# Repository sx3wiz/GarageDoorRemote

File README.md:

# GarageDoorRemote

This project is an OSHW garage door keychain remote and receiver. This project is not garage door opener brand specific. It takes advantage of the fact that almost all garage dooor openers have a NO contact input to trigger a opening/closing cycle.

## Project Goals

1. Small remote form factor
 * Keychain sized
2. Long battery life on remote
3. High security
 * No replay attacks
 * Secure encryption during pairing
3. Decent range
 * About 25 meters

## Directory Structure
* hardware/
 * Contains all OSHW designs for the remote and receiver
* software/
 * Contains all software for remote and receiver

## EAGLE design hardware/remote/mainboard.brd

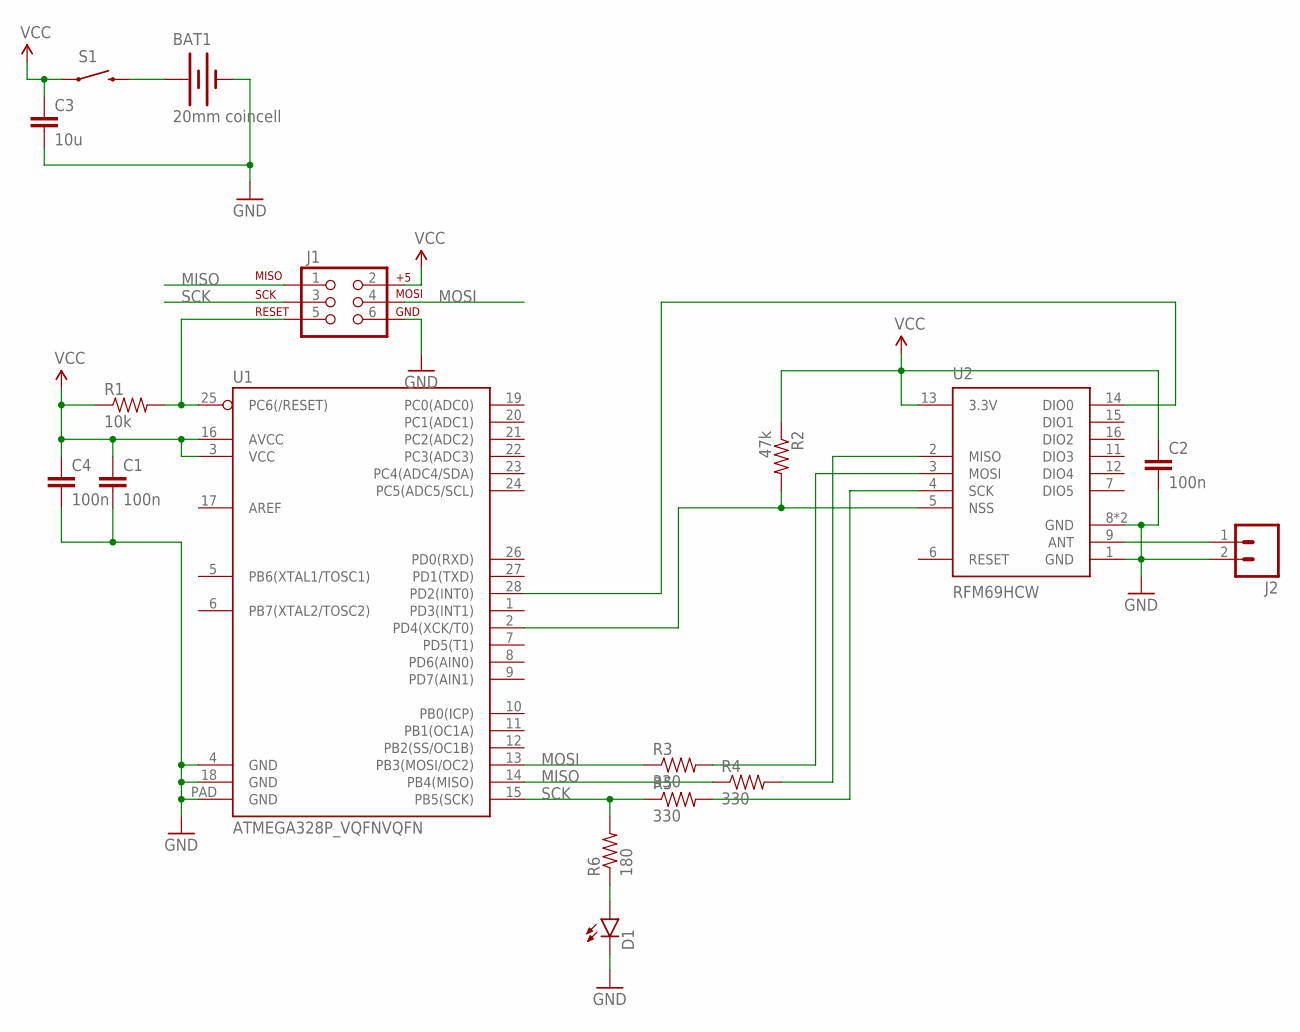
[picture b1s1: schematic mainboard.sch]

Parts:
BAT1: 20mm coincell; BATTCON_20MM_4LEGS
C1, C2, C4: 100n; 0603-CAP
C3: 10u; 1206
D1: LED0603; LED-0603
J1: AVR_SPI_PRG_6PTH; 2X3
J2: M02PTH; 1X02
R1: 10k; 0603-RES
R2: 47k; 0603-RES
R3, R4, R5: 330; 0603-RES
R6: 180; 0603-RES
S1: SWITCH-MOMENTARY-2PTH; TACTILE-PTH
U1: ATMEGA328P_VQFNVQFN; VQFN-28
U2: RFM69HCW; RFM69HCW-XXXS2

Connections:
GND: BAT1.NEGATIVE (-), C1.2, C2.2, C3.2, C4.2, D1.C, J1.6, J2.2, U1.4 (GND), U1.18 (GND), U1.PAD (GND), U2.1 (GND), U2.8 (GND), U2.10 (GND)
MISO: J1.1, R4.1, U1.14 (PB4(MISO))
MOSI: J1.4, R3.1, U1.13 (PB3(MOSI/OC2))
unnamed: BAT1.POSITIVE@1 (+), BAT1.POSITIVE@2 (+), BAT1.POSITIVE@3 (+), BAT1.POSITIVE@4 (+), S1.3 (2)
unnamed: J1.5, R1.2, U1.25 (PC6(/RESET))
unnamed: R3.2, U2.3 (MOSI)
unnamed: J2.1, U2.9 (ANT)
unnamed: R4.2, U2.2 (MISO)
unnamed: R2.2, U1.2 (PD4(XCK/T0)), U2.5 (NSS)
unnamed: R5.2, U2.4 (SCK)
unnamed: U1.28 (PD2(INT0)), U2.14 (DIO0)
unnamed: D1.A, R6.1
SCK: J1.3, R5.1, R6.2, U1.15 (PB5(SCK))
VCC: C1.1, C2.1, C3.1, C4.1, J1.2, R1.1, R2.1, S1.1, U1.3 (VCC), U1.16 (AVCC), U2.13 (3.3V)

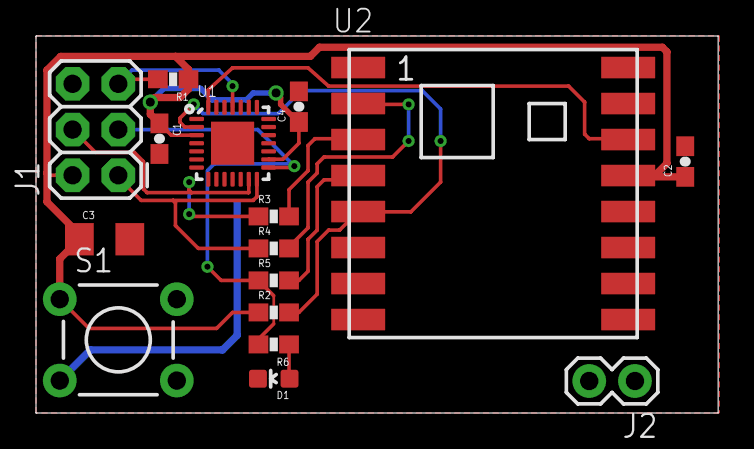
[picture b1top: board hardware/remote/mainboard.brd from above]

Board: 2 copper layers, 37.9 x 20.9 mm, 17 parts (1 on the bottom side), 14 nets.

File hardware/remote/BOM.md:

# Bill of materials

### Version vX.X

Componet Refs  | Type            | Value       | Package  | Qty | Digikey Part #
---------------|-----------------|-------------|----------|-----|---------------
U1             | microcontroller | n/a         | 28-VQFN  | 1   | ATMEGA328P-MMH-ND
U2             | transceiver     | 433mhz      | 16-smd   | 1   | 1568-1391-ND
R1             | resistor        | 10k         | 0603     | 1   | 311-10.0KLRCT-ND
R2             | resistor        | 47k         | 0603     | 1   | P47KJCT-ND
C1, C2         | capacitor       | 100nF/16V   | 0603     | 2   | 490-3261-1-ND
C3             | capacitor       | 10uF/6.3V   | 0603     | 1   | 490-3896-1-ND
S1             | switch          | Mom. NO     | 4-pth    | 1   | (Sparkfun) COM-00097
BAT1           | battery holder  | 20mm        | 4-smd    | 1   | (Sparkfun) PRT-11892
J1             | male header     | n/a         | 6x2 0.1" | 1   | n/a

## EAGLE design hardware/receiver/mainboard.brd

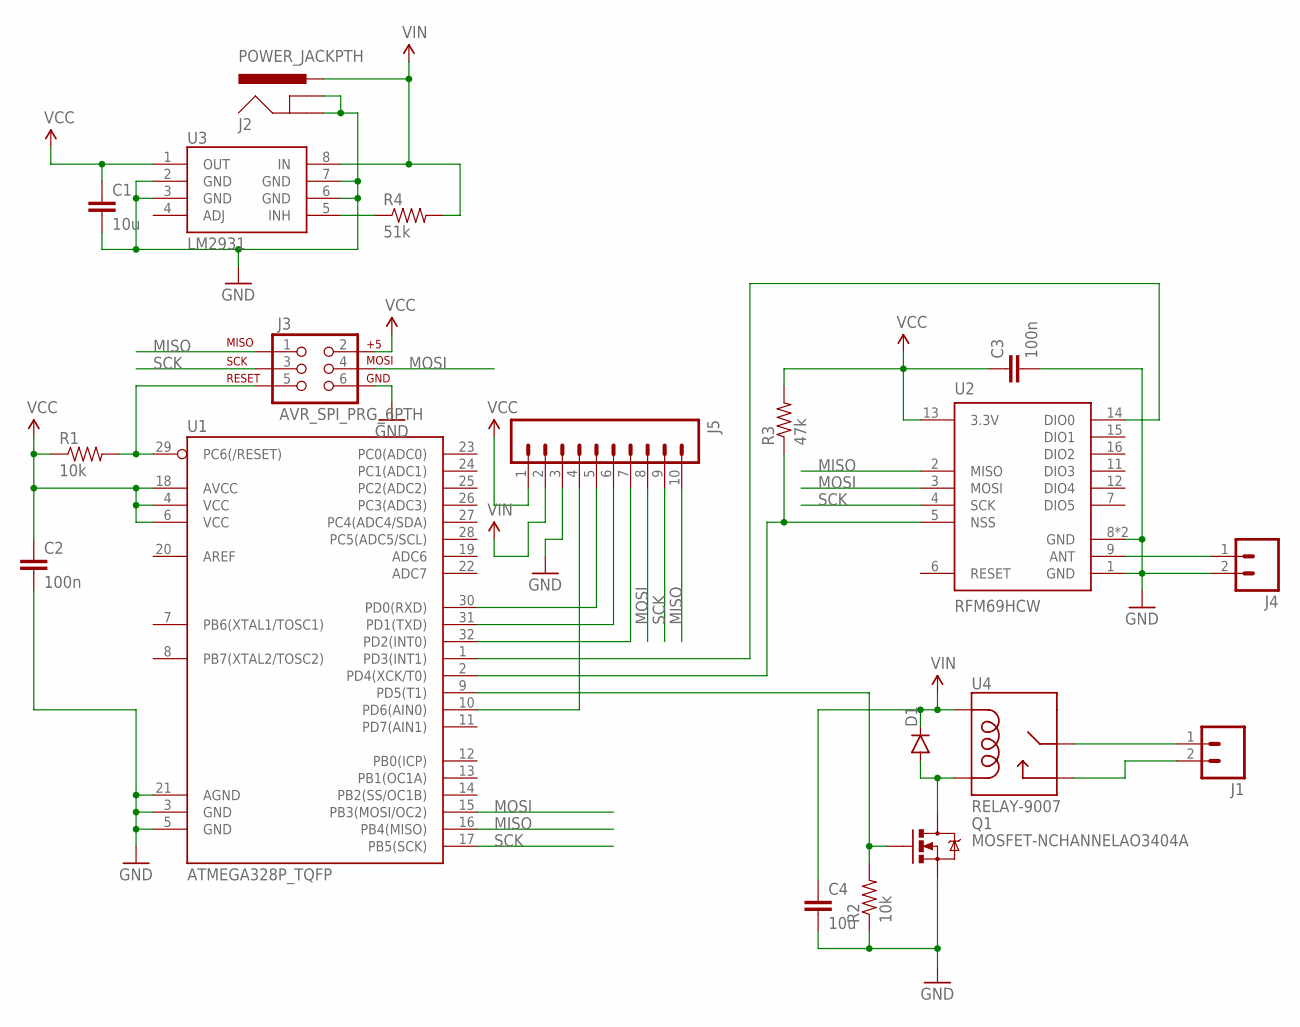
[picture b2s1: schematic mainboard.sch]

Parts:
C1, C4: 10u; 1206
C2, C3: 100n; 0603-CAP
D1: DIODEBAS16; SOD-323
J1: M025MM; SCREWTERMINAL-5MM-2
J2: POWER_JACKPTH; POWER_JACK_PTH
J3: AVR_SPI_PRG_6PTH; 2X3
J4: M02PTH; 1X02
J5: M10SILK_FEMALE_PTH; 1X10
Q1: MOSFET-NCHANNELAO3404A; SOT23-3
R1, R2: 10k; 0603-RES
R3: 47k; 0603-RES
R4: 51k; 0603-RES
U1: ATMEGA328P_TQFP; TQFP32-08
U2: RFM69HCW; RFM69HCW-XXXS2
U3: LM2931; SO08
U4: RELAY-9007

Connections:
GND: C1.2, C2.2, C3.2, C4.2, J2.GND, J2.GNDBREAK, J3.6, J4.2, J5.3, Q1.2 (S), R2.1, U1.3 (GND), U1.5 (GND), U1.21 (AGND), U2.1 (GND), U2.8 (GND), U2.10 (GND), U3.2 (GND), U3.3 (GND), U3.6 (GND), U3.7 (GND)
MISO: J3.1, J5.10, U1.16 (PB4(MISO)), U2.2 (MISO)
MOSI: J3.4, J5.8, U1.15 (PB3(MOSI/OC2)), U2.3 (MOSI)
unnamed: R3.1, U1.2 (PD4(XCK/T0)), U2.5 (NSS)
unnamed: J3.5, R1.2, U1.29 (PC6(/RESET))
unnamed: U1.1 (PD3(INT1)), U2.14 (DIO0)
unnamed: J4.1, U2.9 (ANT)
unnamed: J1.1, U4.1 (MAIN)
unnamed: J1.2, U4.4 (NO)
unnamed: D1.A, Q1.3 (D), U4.3 (COIL2)
unnamed: Q1.1 (G), R2.2, U1.9 (PD5(T1))
unnamed: J5.7, U1.32 (PD2(INT0))
unnamed: J5.6, U1.31 (PD1(TXD))
unnamed: J5.5, U1.30 (PD0(RXD))
unnamed: J5.4, U1.10 (PD6(AIN0))
unnamed: R4.1, U3.5 (INH)
SCK: J3.3, J5.9, U1.17 (PB5(SCK)), U2.4 (SCK)
VCC: C1.1, C2.1, C3.1, J3.2, J5.1, R1.1, R3.2, U1.4 (VCC), U1.6 (VCC), U1.18 (AVCC), U2.13 (3.3V), U3.1 (OUT)
VIN: C4.1, D1.C, J2.PWR, J5.2, R4.2, U3.8 (IN), U4.2 (COIL1)

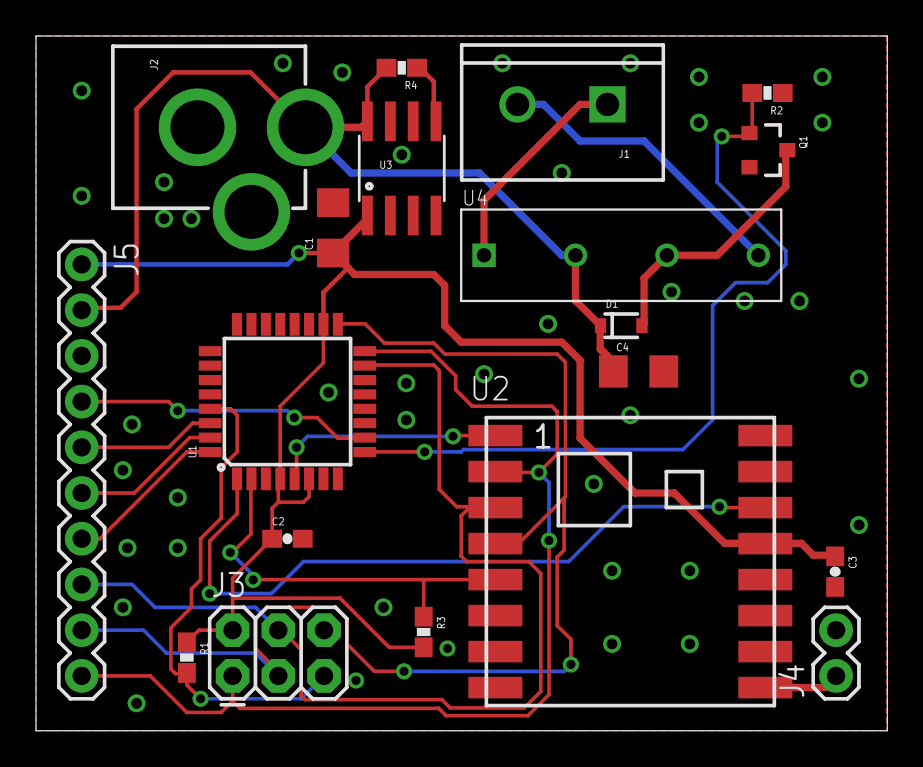
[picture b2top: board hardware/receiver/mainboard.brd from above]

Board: 2 copper layers, 47.3 x 38.6 mm, 19 parts (0 on the bottom side), 19 nets.

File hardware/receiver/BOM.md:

# Bill of materials

### Version vX.X

Componet Refs  | Type            | Value       | Package  | Qty | Digikey Part #
---------------|-----------------|-------------|----------|-----|---------------
U1             | microcontroller | n/a         | 32-TQFP  | 1   | ATMEGA328P-AU-ND
U2             | transceiver     | 433mhz      | 16-smd   | 1   | 1568-1391-ND
U3             | linear regulator| 3.3v/100ma  | SOIC-8   | 1   | 497-6880-1-ND
R1, R2         | resistor        | 10k         | 0603     | 2   | 311-10.0KLRCT-ND
R3             | resistor        | 47k         | 0603     | 1   | P47KJCT-ND
C1             | capacitor       | 10uF/6.3V   | 0603     | 1   | 490-3896-1-ND
C2, C3         | capacitor       | 100nF/16V   | 0603     | 2   | 490-3261-1-ND
Q1             | n-ch mosfet     | Id=4.3A     | SOT-23-3 | 1   | BSS214N H6327CT-ND
D1, D2         | diode           | Io=1A       | SOD-323  | 2   | SBR130S3-7DICT-ND
U4             | relay           | SPST        | SIP-4    | 1   | 306-1062-ND
J2             | barrel jack     | n/a         | 5.5x2.1mm| 1   | (Sparkfun) PRT-10811
J1             | screw terminal  | n/a         | 1x2 5mm  | 1   | n/p
J3             | male header     | n/a         | 6x2 0.1" | 1   | n/p
J4             | male header     | n/a         | 1x2 0.1" | 1   | n/p
J5             | male header     | n/a         | 1x10 0.1"| 1   | n/p

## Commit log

2016-07-14 Revised README
2016-07-14 modified README
2016-07-16 Added parts to schematic
2016-07-16 Added .gitignore file
2016-07-16 Scehamtic work
2016-07-16 Preliminary schematic design
2016-07-16 PCB component placement and antenna connector
2016-07-16 Preliminary PCB design
2016-07-16 Added components to receiver schematic
2016-07-17 Preliminary schematic
2016-07-17 Added expansion connector
2016-07-17 Initial PCB layout
    * Optimized expansion connector for PCB layout
    * Added protection diode to relay
2016-07-23 Added BOM and modified resistor value
    Remote
    * Added detailed BOM with digikey part numbers.
    * Changed R2 from 50k to 47k as 47k is a much more common value.
2016-07-23 Added BOM and diode protection
    Receiver
    * Added BOM
    * Issue with relay activation voltage
    * Had to change VIN to 5V and add a regulator to 3.3B
    * Added VIN pin to expansion header
2016-07-23 Initial PCB layout of Receiver
    Receiver
    * Changed expansion connector pinout to make layout easier
2016-07-23 Fixed wrong MCU in BOM for receiver
2016-07-23 Fixed SPI mismatch
2016-07-23 fixed part mistake
2016-09-13 Replaced relay and voltage regulator in schematic
2016-09-14 Replaced LDO and relay and updated BOM
2016-09-14 Added ground plane vias
2016-09-27 Added frames
2016-09-30 Added SPI series impedance and status LED

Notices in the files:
parts and their libraries:
SparkFun-Passives: Licensing: Creative Commons ShareAlike 4.0 International - https://creativecommons.org/licenses/by-sa/4.0
